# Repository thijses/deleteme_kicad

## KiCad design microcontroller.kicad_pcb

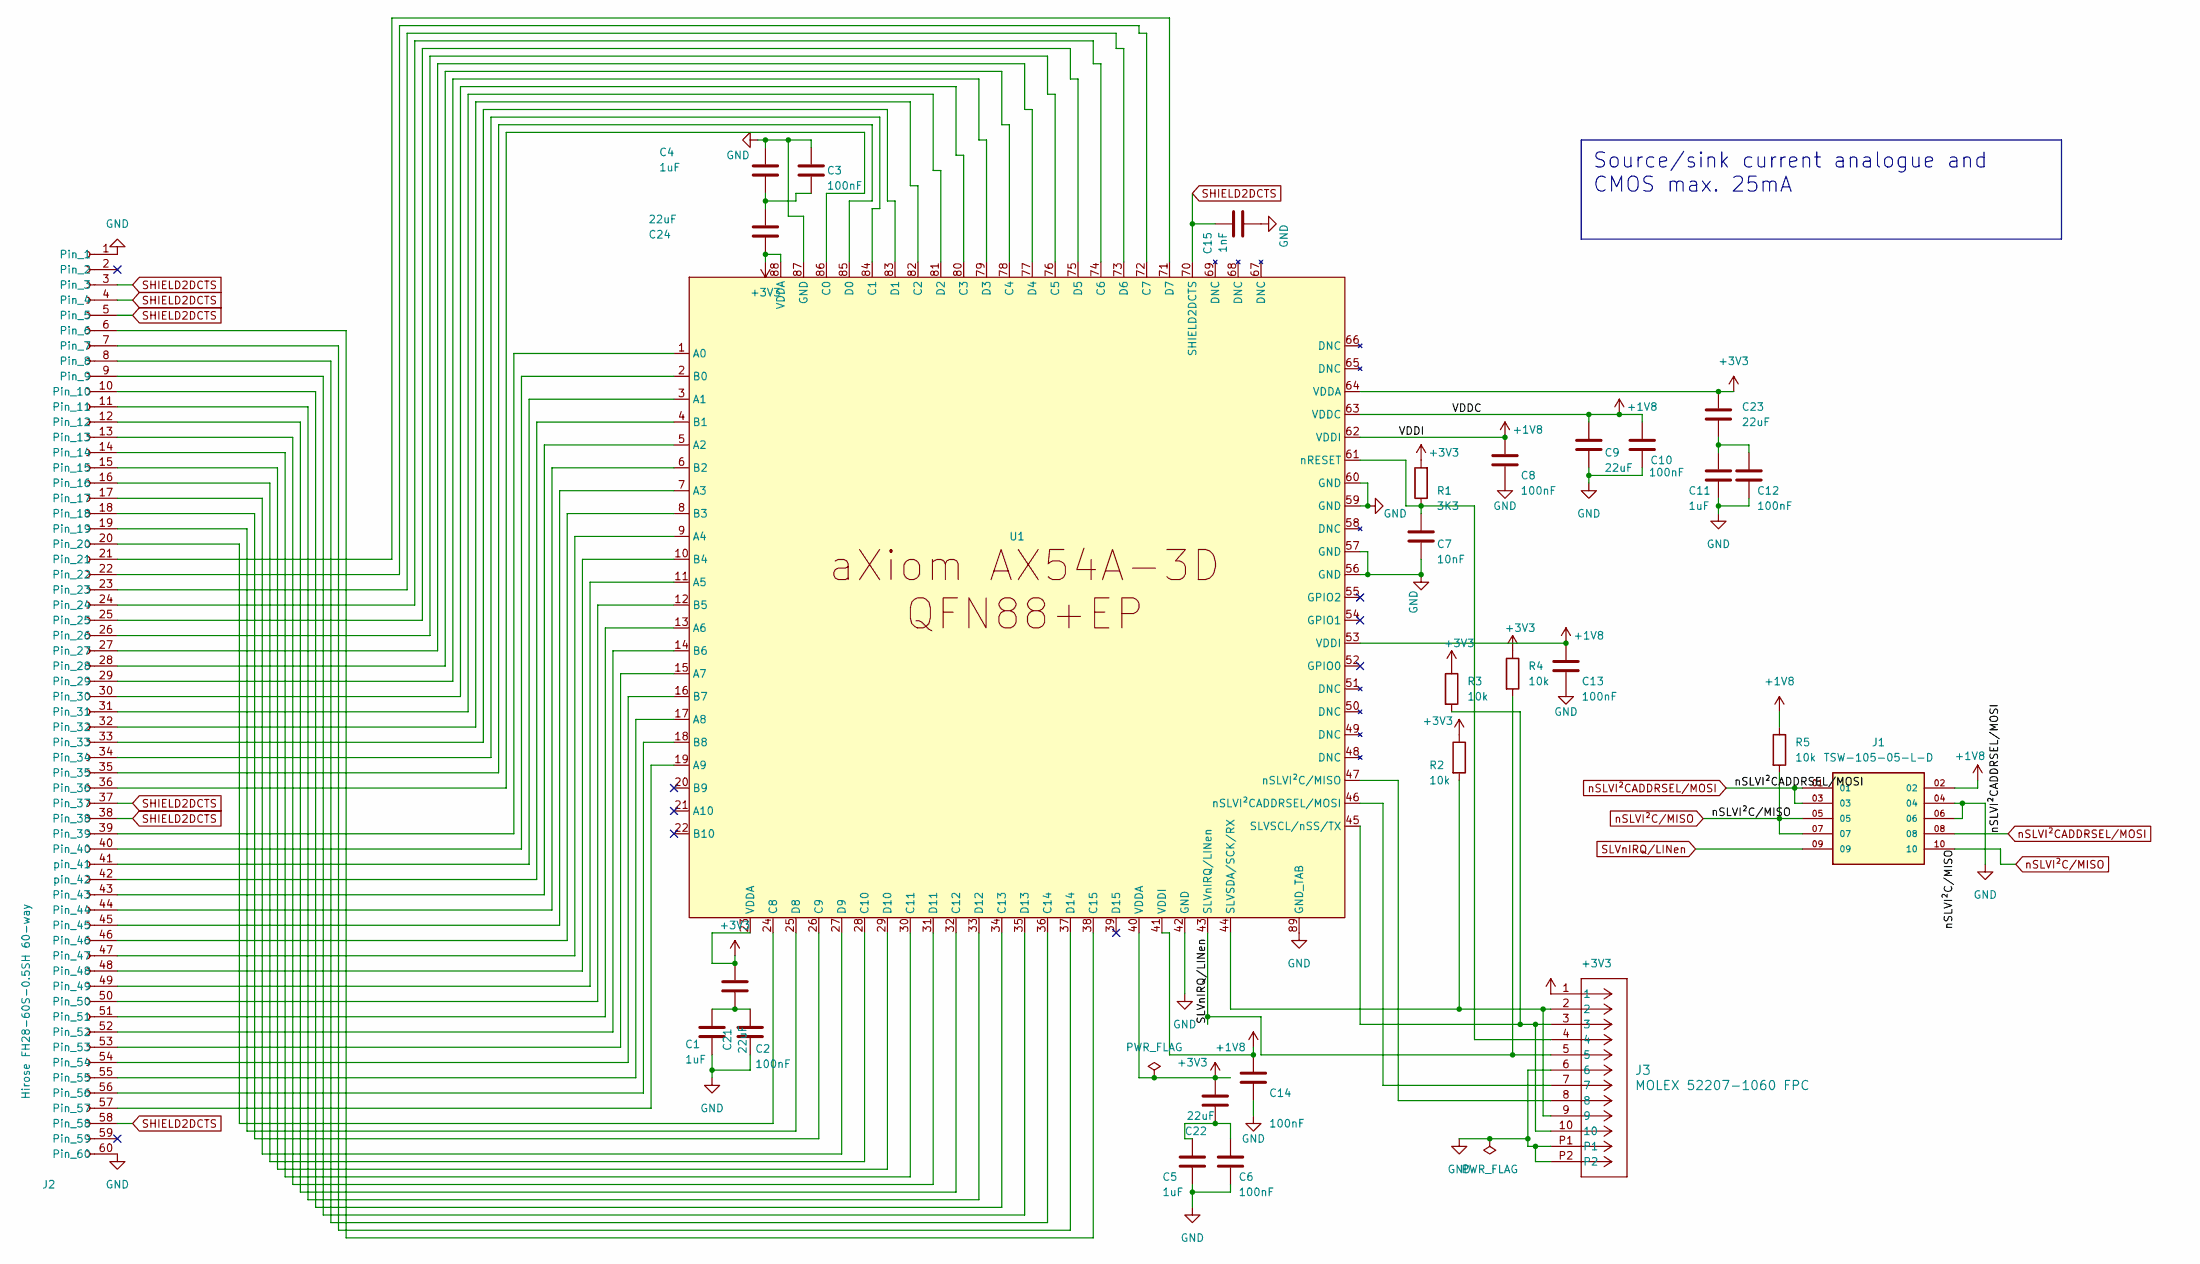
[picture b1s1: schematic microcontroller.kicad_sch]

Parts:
C1, C4, C5, C11: 1uF; C_0805_2012Metric_Pad1.18x1.45mm_HandSolder
C2, C3, C6, C8, C10, C12, C13, C14: 100nF; C_1206_3216Metric_Pad1.33x1.80mm_HandSolder
C7: 10nF; C_1206_3216Metric_Pad1.33x1.80mm_HandSolder
C9: 22uF; C_0402_1005Metric_Pad0.74x0.62mm_HandSolder
C15: 1nF; C_0402_1005Metric_Pad0.74x0.62mm_HandSolder
C21, C22, C23, C24: 22uF; C_0805_2012Metric_Pad1.18x1.45mm_HandSolder
J1: TSW-105-05-L-D; SAMTEC_TSW-105-05-L-D; PARTREV R
J2: Hirose FH28-60S-0.5SH 60-way; HRS_FH28-60S-0.5SH_05_
J3: MOLEX 52207-1060 FPC; CON_522071060_MOL
R1: 3K3; R_2512_6332Metric_Pad1.40x3.35mm_HandSolder
R2, R3, R4, R5: 10k; R_1210_3225Metric_Pad1.30x2.65mm_HandSolder
U1: QFN-88_EP_9.8x9.8_Pitch0.4mm

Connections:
+1V8: C8.1, C9.1, C10.1, C13.1, C14.1, J1.02, R5.1, U1.41 (VDDI), U1.53 (VDDI), U1.62 (VDDI), U1.63 (VDDC)
+3V3: C21.1, C22.2, C23.1, C24.1, J3.1, R1.2, R2.1, R3.1, R4.1, U1.23 (VDDA), U1.40 (VDDA), U1.64 (VDDA), U1.88 (VDDA)
GND: C1.2, C2.2, C3.1, C4.1, C5.2, C6.2, C7.2, C8.2, C9.2, C10.2, C11.2, C12.2, C13.2, C14.2, C15.2, J1.04, J1.06, J2.1, J2.60, J3.6, J3.P1, J3.P2, U1.42 (GND), U1.56 (GND), U1.57 (GND), U1.59 (GND), U1.60 (GND), U1.87 (GND), U1.89 (GND_TAB)
unnamed: C1.1, C2.1, C21.2
unnamed: C11.1, C12.1, C23.2
unnamed: C5.1, C6.1, C22.1
unnamed: C3.2, C4.2, C24.2
unnamed: J2.6, U1.38 (C15)
unnamed: J2.7, U1.37 (D14)
unnamed: J2.8, U1.36 (C14)
unnamed: J2.9, U1.35 (D13)
unnamed: J2.10, U1.34 (C13)
unnamed: J2.11, U1.33 (D12)
unnamed: J2.12, U1.32 (C12)
unnamed: J2.13, U1.31 (D11)
unnamed: J2.14, U1.30 (C11)
unnamed: J2.15, U1.29 (D10)
unnamed: J2.16, U1.28 (C10)
unnamed: J2.17, U1.27 (D9)
unnamed: J2.18, U1.26 (C9)
unnamed: J2.19, U1.25 (D8)
unnamed: J2.20, U1.24 (C8)
unnamed: J2.21, U1.71 (D7)
unnamed: J2.22, U1.72 (C7)
unnamed: J2.23, U1.73 (D6)
unnamed: J2.24, U1.74 (C6)
unnamed: J2.25, U1.75 (D5)
unnamed: J2.26, U1.76 (C5)
unnamed: J2.27, U1.77 (D4)
unnamed: J2.28, U1.78 (C4)
unnamed: J2.29, U1.79 (D3)
unnamed: J2.30, U1.80 (C3)
unnamed: J2.31, U1.81 (D2)
unnamed: J2.32, U1.82 (C2)
unnamed: J2.33, U1.83 (D1)
unnamed: J2.34, U1.84 (C1)
unnamed: J2.35, U1.85 (D0)
unnamed: J2.36, U1.86 (C0)
unnamed: J2.39, U1.1 (A0)
unnamed: J2.40, U1.2 (B0)
unnamed: J2.43, U1.5 (A2)
unnamed: J2.44, U1.6 (B2)
unnamed: J2.45, U1.7 (A3)
unnamed: J2.46, U1.8 (B3)
unnamed: J2.47, U1.9 (A4)
unnamed: J2.48, U1.10 (B4)
unnamed: J2.49, U1.11 (A5)
unnamed: J2.50, U1.12 (B5)
unnamed: J2.51, U1.13 (A6)
unnamed: J2.52, U1.14 (B6)
unnamed: J2.53, U1.15 (A7)
unnamed: J2.54, U1.16 (B7)
unnamed: J2.55, U1.17 (A8)
unnamed: J2.56, U1.18 (B8)
unnamed: J2.57, U1.19 (A9)
unnamed: J2.41 (pin), U1.3 (A1)
unnamed: J2.42 (pin), U1.4 (B1)
unnamed: C7.1, J3.4, R1.1, U1.61 (nRESET)
SHIELD2DCTS: C15.1, J2.3, J2.4, J2.5, J2.37, J2.38, J2.58, U1.70 (SHIELD2DCTS)
SLVSCL/nSS/TX: J3.3, J3.10, R3.2, U1.45 (SLVSCL/nSS/TX)
SLVSDA/SCK/RX: J3.2, J3.9, R2.2, U1.44 (SLVSDA/SCK/RX)
SLVnIRQ/LINen: J1.09, J3.5, R4.2, U1.43 (SLVnIRQ/LINen)

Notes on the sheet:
Source/sink current analogue and CMOS max. 25mA

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
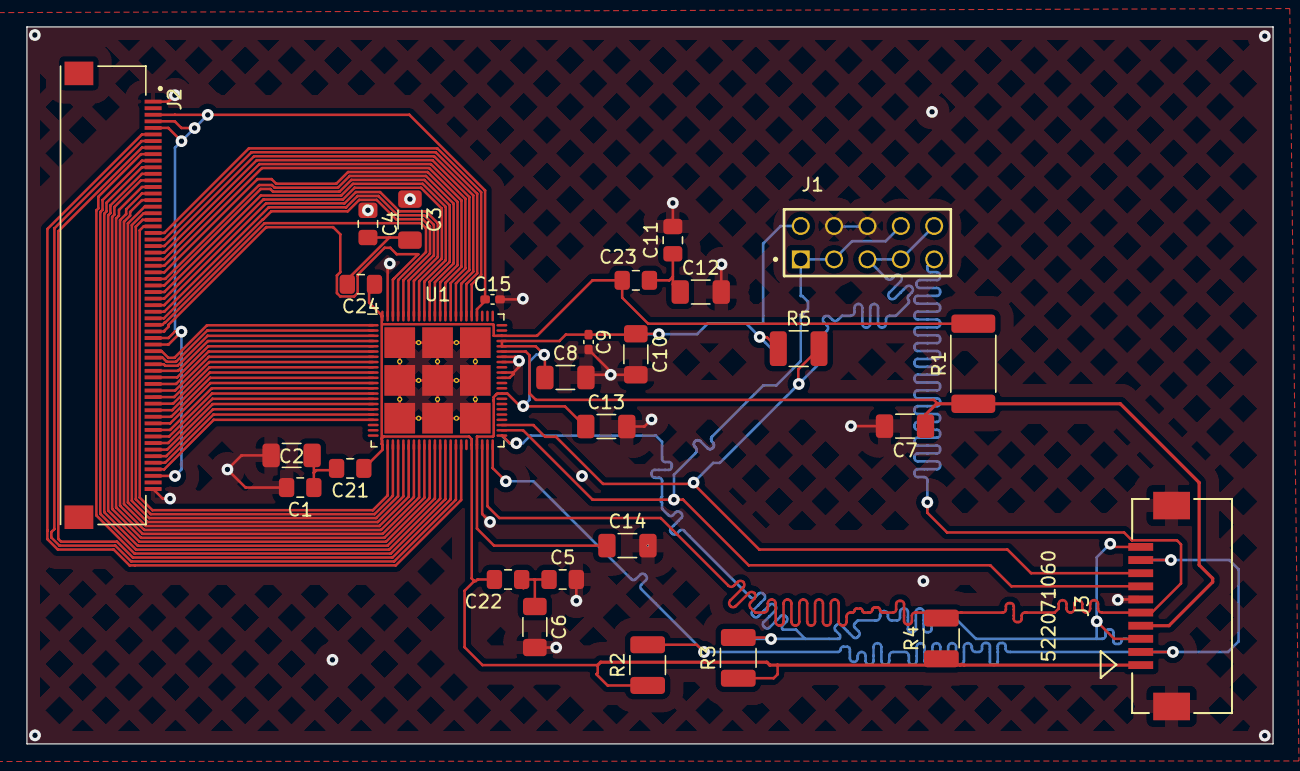
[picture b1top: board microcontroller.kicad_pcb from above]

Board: 2 copper layers, 94.9 x 54.6 mm, 28 parts (0 on the bottom side), 64 nets.

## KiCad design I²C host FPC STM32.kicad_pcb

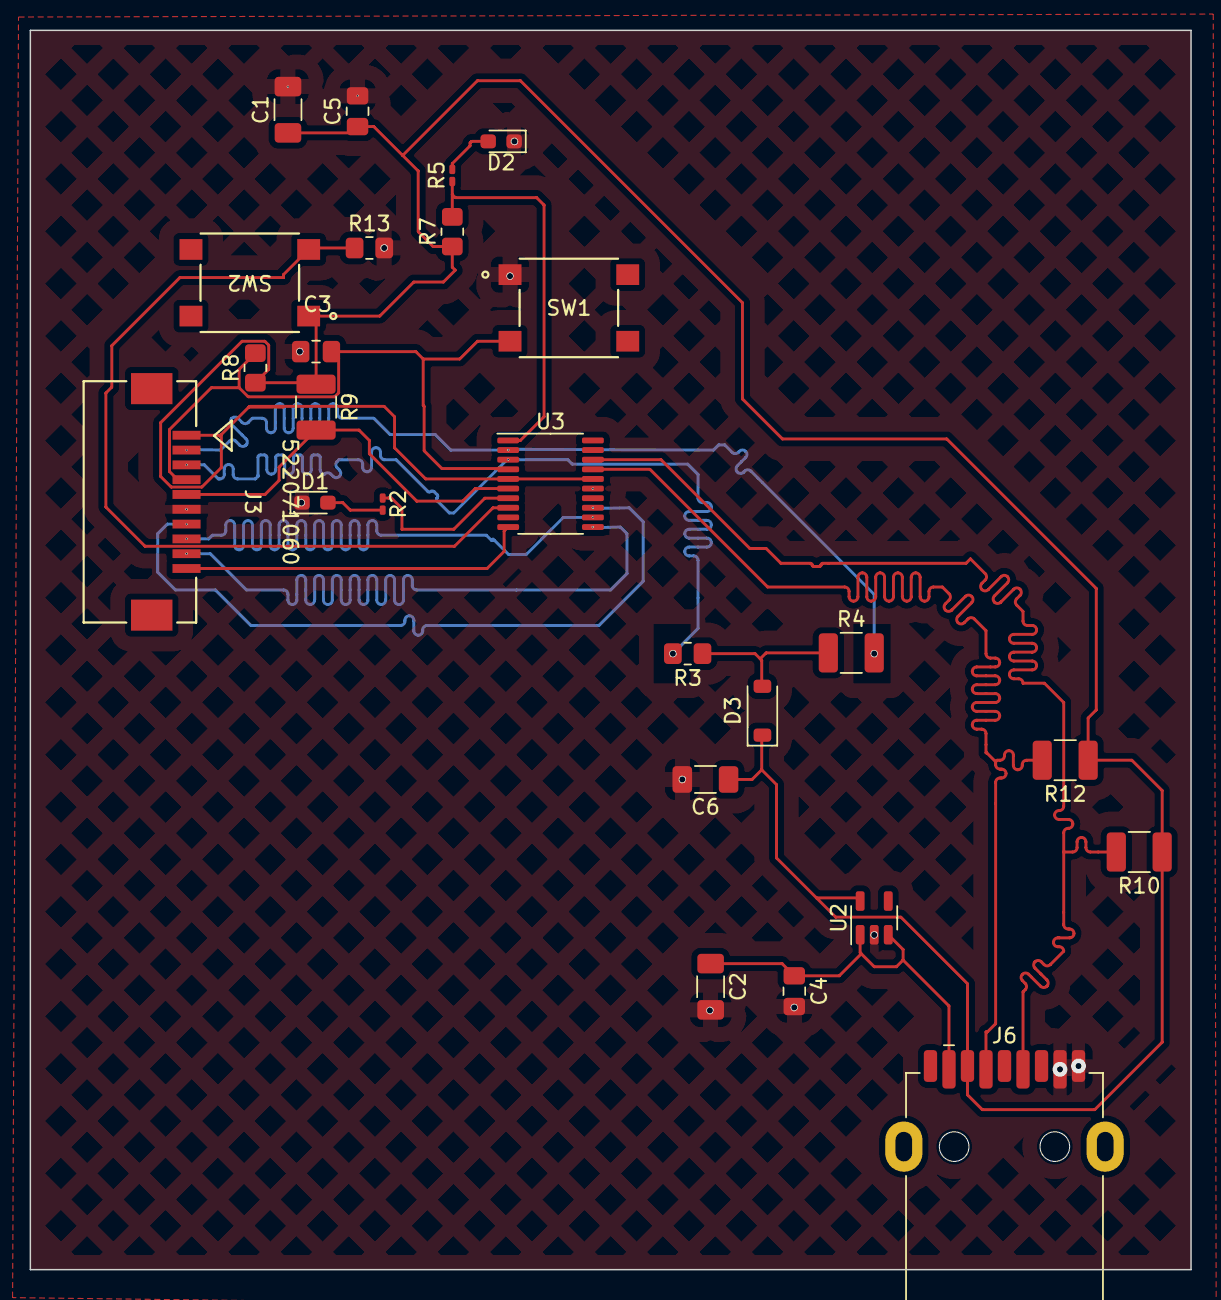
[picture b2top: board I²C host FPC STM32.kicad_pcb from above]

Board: 2 copper layers, 78.4 x 83.7 mm, 25 parts (0 on the bottom side), 19 nets.

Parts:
C1, C2, C6: 100nF; C_1206_3216Metric_Pad1.33x1.80mm_HandSolder
C3: 40nF; C_0805_2012Metric_Pad1.18x1.45mm_HandSolder
C4: 470nF; C_0805_2012Metric_Pad1.18x1.45mm_HandSolder
C5: 1uF; C_0805_2012Metric_Pad1.18x1.45mm_HandSolder
D1: LEDaxiom; D_0603_1608Metric_Pad1.05x0.95mm_HandSolder
D2: LEDusb; D_0603_1608Metric_Pad1.05x0.95mm_HandSolder
D3: 3,3V zener; D_SOD-123
J3: Aansluiting converter (aangesloten aan chipboard); CON_522071060_MOL
J6: USB_A; USB3_A_Receptacle_Wuerth_692122030100
R2, R5: 1k; R_0201_0603Metric_Pad0.64x0.40mm_HandSolder
R3: 8,8k; R_0805_2012Metric_Pad1.20x1.40mm_HandSolder
R4, R9: 10k; R_1210_3225Metric_Pad1.30x2.65mm_HandSolder
R7, R13: 25k; R_0805_2012Metric_Pad1.20x1.40mm_HandSolder
R8: 5k; R_0805_2012Metric_Pad1.20x1.40mm_HandSolder
R10, R12: 220k; R_1210_3225Metric_Pad1.30x2.65mm_HandSolder
SW1: reset switch; SO4_222A-M-V-B_CTS
SW2: Boot switch; SO4_222A-M-V-B_CTS
U2: AP2112K-3.3; SOT-23-5
U3: STM32F042F6; TSSOP-20_4.4x6.5mm_P0.65mm

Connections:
+3V3: C1.1, C5.1, C6.1, D3.1 (K), J3.1, J6.8, R7.1, R8.1, R9.1, R10.1, R12.1, SW2.1, U2.5 (VOUT), U3.5 (VDD), U3.16 (VDD)
+5V: C2.1, C4.1, J6.1 (VBUS), U2.1 (VIN), U2.3 (EN)
/Boot0/LEDusb: R5.1, R7.2, U3.1 (Boot0/LEDusb)
/COMMS_sel: R13.1, SW2.2, U3.8 (COMMS_sel)
/D+: J6.3 (D+), R10.2, U3.18 (D+)
/D-: J6.2 (D-), R12.2, U3.17 (D-)
/LEDaxiom: R2.1, U3.7 (LEDaxiom)
/Zenerdiode: D3.2 (A), R3.1, R4.1
GND: C1.2, C2.2, C3.2, C4.2, C5.2, C6.2, D1.1 (K), D2.1 (K), J3.6, J6.4 (GND), J6.5 (Shield), R13.2, SW1.1, U2.2 (GND), U3.15 (VSS)
MISO: J3.8, U3.12 (SPI_miso)
MOSI: J3.7, U3.13 (SPI_mosi)
unnamed: D1.2 (A), R2.2
unnamed: D2.2 (A), R5.2
SCK: J3.9, U3.11 (SPI_sck)
SCL: J3.3, R3.2, U3.3 (i2c_sclk)
SDA: J3.2, R4.2, U3.2 (i2c_sda)
SLVSCL/nSS axiom: J3.10, U3.10 (SPI_nss)
SLVnIRQ axiom: J3.5, R9.2, U3.6 (nIRQ)
nRST: C3.1, J3.4, R8.2, SW1.2, U3.4 (NRST)
